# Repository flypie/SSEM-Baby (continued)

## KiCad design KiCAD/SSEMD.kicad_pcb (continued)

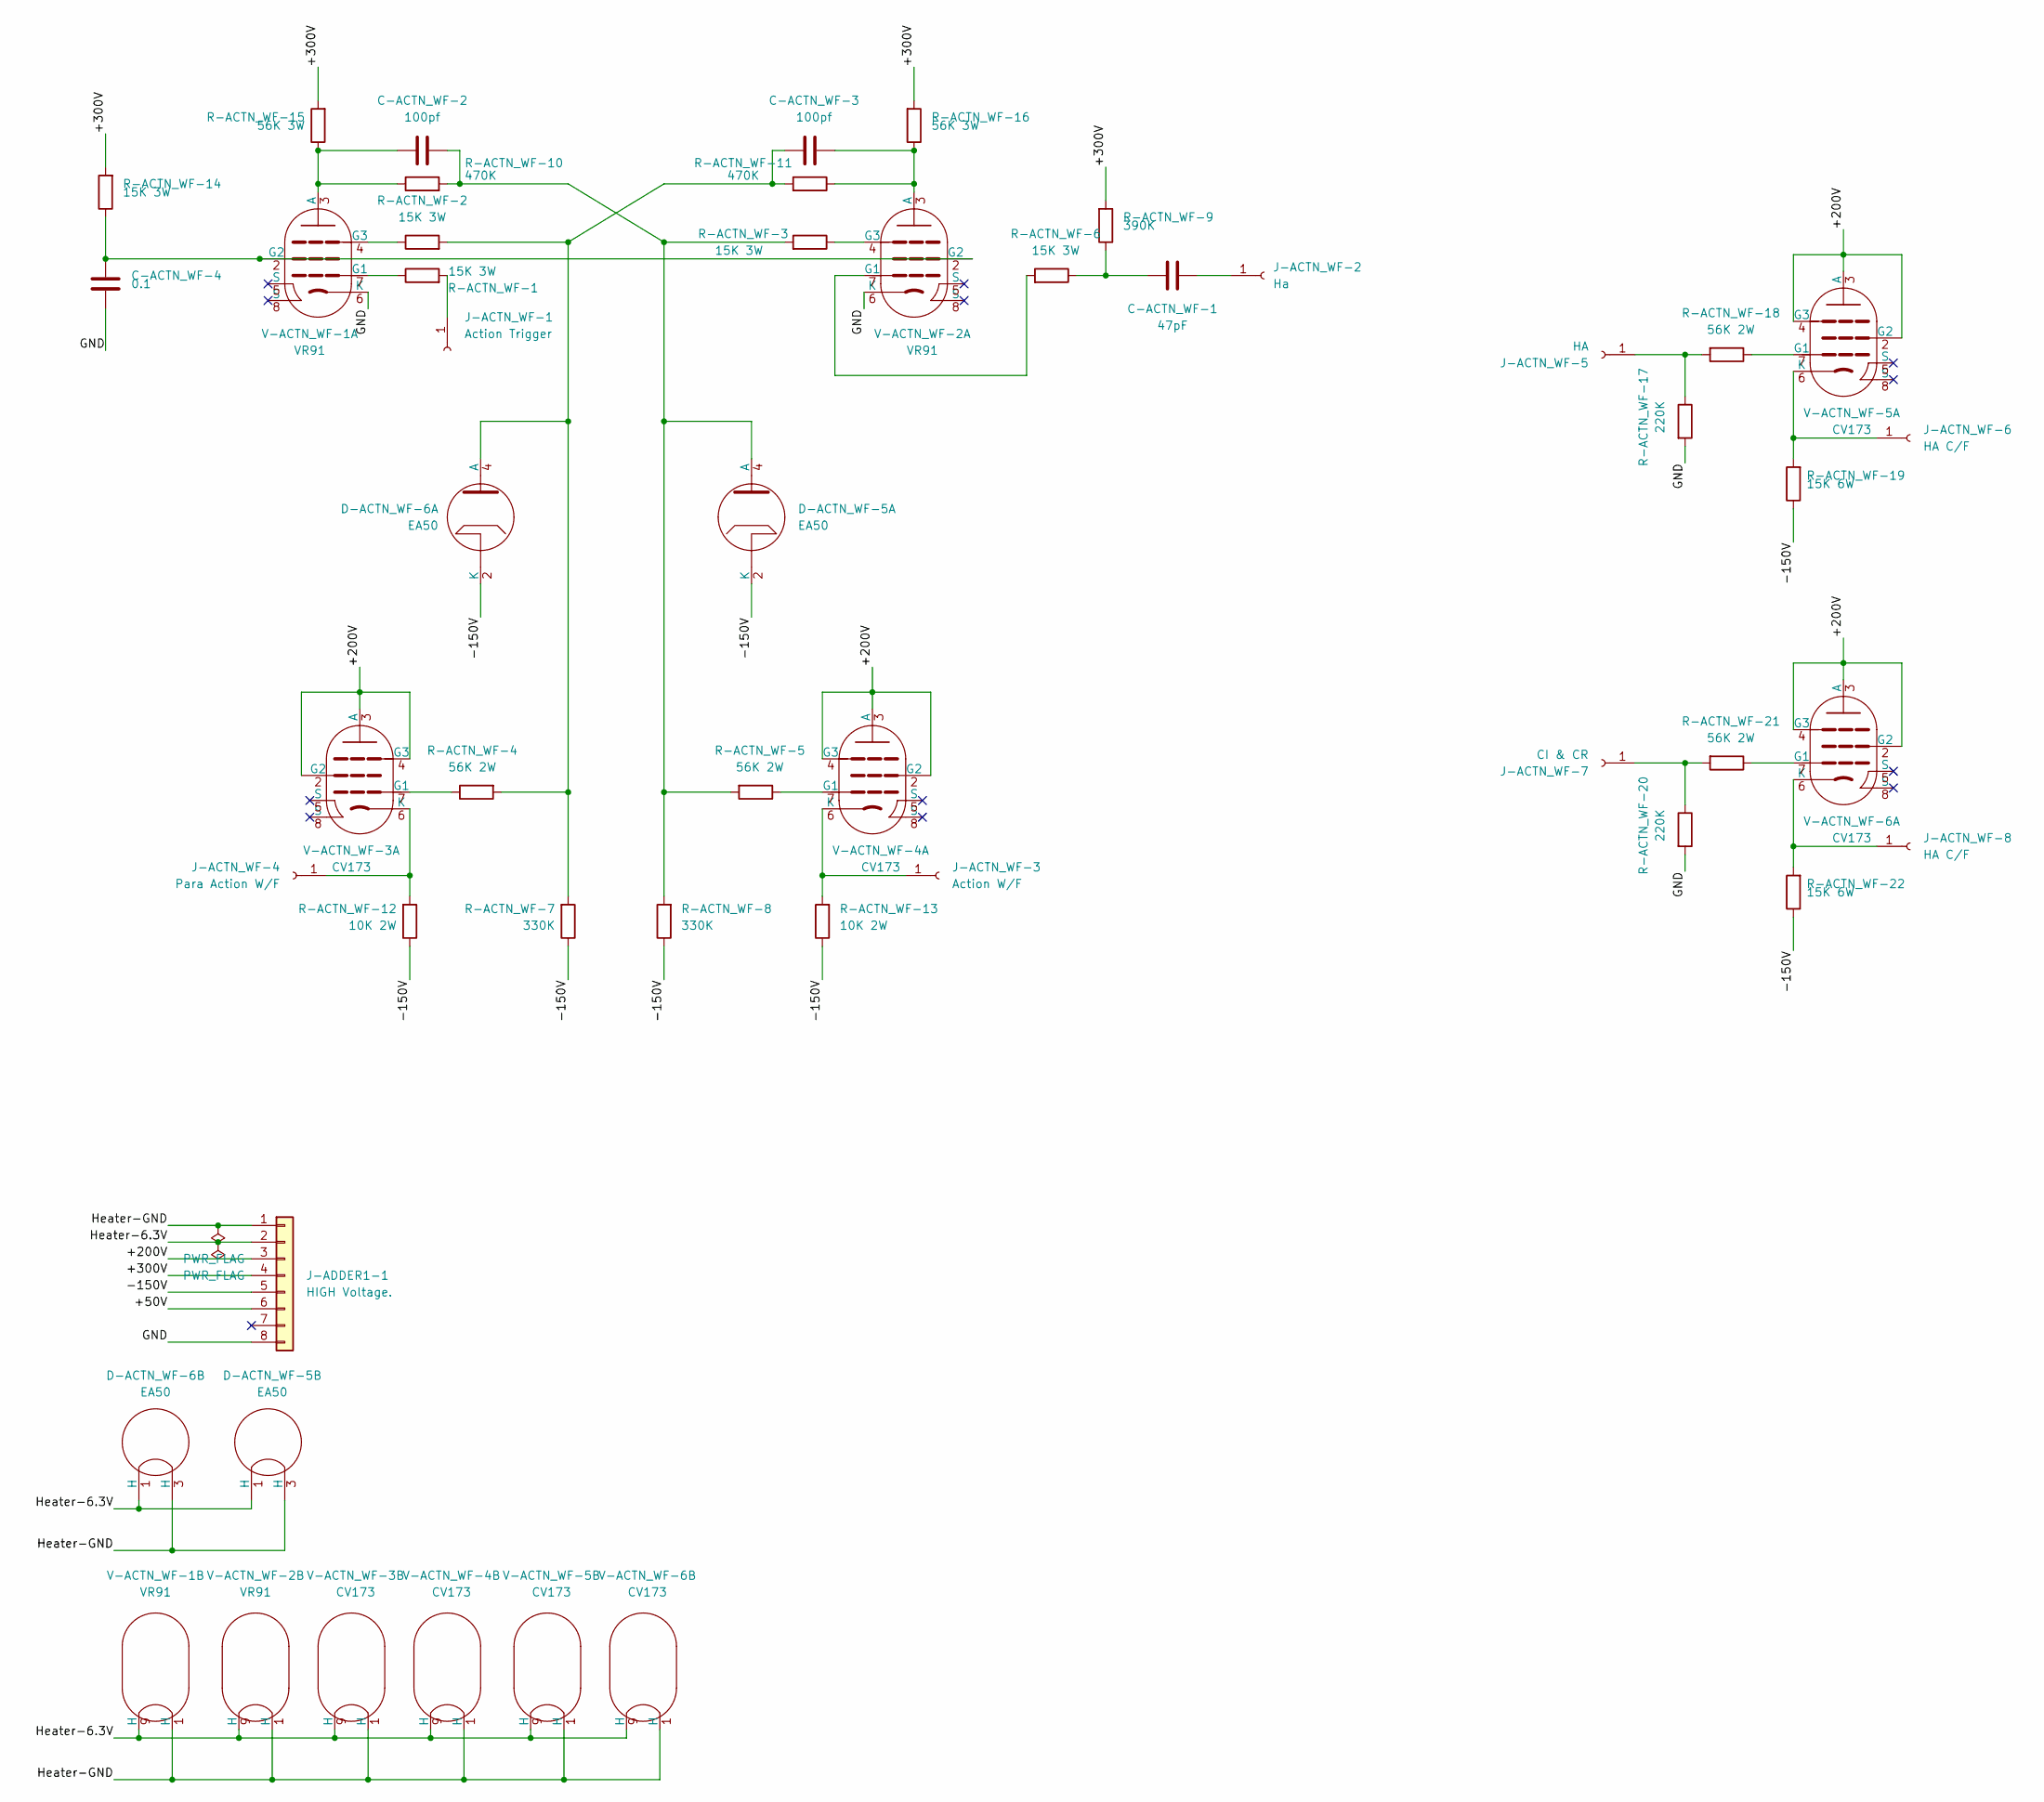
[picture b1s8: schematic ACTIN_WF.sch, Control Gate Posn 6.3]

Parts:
C-ACTN_WF-1: 47pF; C_Disc_D7.5mm_W5.0mm_P5.00mm
C-ACTN_WF-2, C-ACTN_WF-3: 100pf; C_Disc_D7.5mm_W5.0mm_P5.00mm
C-ACTN_WF-4: 0.1; C_Disc_D7.5mm_W5.0mm_P5.00mm
D-ACTN_WF-5, D-ACTN_WF-6: EA50; Valve_B3G
J-ACTN_WF-1: Action Trigger; 242431
J-ACTN_WF-2: Ha; 242431
J-ACTN_WF-3: Action W/F; 242431
J-ACTN_WF-4: Para Action W/F; 242431
J-ACTN_WF-5: HA; 242431
J-ACTN_WF-6, J-ACTN_WF-8: HA C/F; 242431
J-ACTN_WF-7: CI & CR; 242431
J-ADDER1-1: HIGH Voltage.; TE_MATE-N-LOK_1-770970-x_2x04_P4.14mm_Horizontal
R-ACTN_WF-1, R-ACTN_WF-2, R-ACTN_WF-3, R-ACTN_WF-6, R-ACTN_WF-14: 15K 3W; R_Axial_DIN0516_L15.5mm_D5.0mm_P5.08mm_Vertical
R-ACTN_WF-4, R-ACTN_WF-5, R-ACTN_WF-18, R-ACTN_WF-21: 56K 2W; R_Axial_DIN0516_L15.5mm_D5.0mm_P5.08mm_Vertical
R-ACTN_WF-7, R-ACTN_WF-8: 330K; R_Axial_DIN0516_L15.5mm_D5.0mm_P5.08mm_Vertical
R-ACTN_WF-9: 390K; R_Axial_DIN0516_L15.5mm_D5.0mm_P5.08mm_Vertical
R-ACTN_WF-10, R-ACTN_WF-11: 470K; R_Axial_DIN0516_L15.5mm_D5.0mm_P5.08mm_Vertical
R-ACTN_WF-12, R-ACTN_WF-13: 10K 2W; R_Axial_DIN0516_L15.5mm_D5.0mm_P5.08mm_Vertical
R-ACTN_WF-15, R-ACTN_WF-16: 56K 3W; R_Axial_DIN0516_L15.5mm_D5.0mm_P5.08mm_Vertical
R-ACTN_WF-17, R-ACTN_WF-20: 220K; R_Axial_DIN0516_L15.5mm_D5.0mm_P5.08mm_Vertical
R-ACTN_WF-19, R-ACTN_WF-22: 15K 6W; R_Axial_DIN0516_L15.5mm_D5.0mm_P5.08mm_Vertical
V-ACTN_WF-1, V-ACTN_WF-2: VR91; Valve_9Loctal
V-ACTN_WF-3, V-ACTN_WF-4, V-ACTN_WF-5, V-ACTN_WF-6: CV173; Valve_9Loctal

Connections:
/ACTIN_WF/+200V: J-ADDER1-1.3, V-ACTN_WF-3.2 (G2), V-ACTN_WF-3.3 (A), V-ACTN_WF-3.4 (G3), V-ACTN_WF-4.2 (G2), V-ACTN_WF-4.3 (A), V-ACTN_WF-4.4 (G3), V-ACTN_WF-5.2 (G2), V-ACTN_WF-5.3 (A), V-ACTN_WF-5.4 (G3), V-ACTN_WF-6.2 (G2), V-ACTN_WF-6.3 (A), V-ACTN_WF-6.4 (G3)
/ACTIN_WF/+300V: J-ADDER1-1.4, R-ACTN_WF-9.2, R-ACTN_WF-14.2, R-ACTN_WF-15.2, R-ACTN_WF-16.2
/ACTIN_WF/-150V: D-ACTN_WF-5.2 (K), D-ACTN_WF-6.2 (K), J-ADDER1-1.5, R-ACTN_WF-7.1, R-ACTN_WF-8.1, R-ACTN_WF-12.1, R-ACTN_WF-13.1, R-ACTN_WF-19.1, R-ACTN_WF-22.1
/ACTIN_WF/GND: C-ACTN_WF-4.2, J-ADDER1-1.8, R-ACTN_WF-17.2, R-ACTN_WF-20.2, V-ACTN_WF-1.6 (K), V-ACTN_WF-2.6 (K)
/ACTIN_WF/Heater-6.3V: D-ACTN_WF-5.1 (H), D-ACTN_WF-6.1 (H), J-ADDER1-1.2, V-ACTN_WF-1.9 (H), V-ACTN_WF-2.9 (H), V-ACTN_WF-3.9 (H), V-ACTN_WF-4.9 (F1), V-ACTN_WF-5.9 (H), V-ACTN_WF-6.9 (H)
/ACTIN_WF/Heater-GND: D-ACTN_WF-5.3 (H), D-ACTN_WF-6.3 (H), J-ADDER1-1.1, V-ACTN_WF-1.1 (H), V-ACTN_WF-2.1 (H), V-ACTN_WF-3.1 (H), V-ACTN_WF-4.1 (F1), V-ACTN_WF-5.1 (H), V-ACTN_WF-6.1 (H)
unnamed: C-ACTN_WF-1.1, J-ACTN_WF-2.1
unnamed: C-ACTN_WF-1.2, R-ACTN_WF-6.1, R-ACTN_WF-9.1
unnamed: C-ACTN_WF-2.1, R-ACTN_WF-10.1, R-ACTN_WF-15.1, V-ACTN_WF-1.3 (A)
unnamed: C-ACTN_WF-2.2, D-ACTN_WF-5.4 (A), R-ACTN_WF-3.2, R-ACTN_WF-5.2, R-ACTN_WF-8.2, R-ACTN_WF-10.2
unnamed: C-ACTN_WF-3.1, R-ACTN_WF-11.1, R-ACTN_WF-16.1, V-ACTN_WF-2.3 (A)
unnamed: C-ACTN_WF-3.2, D-ACTN_WF-6.4 (A), R-ACTN_WF-2.2, R-ACTN_WF-4.2, R-ACTN_WF-7.2, R-ACTN_WF-11.2
unnamed: C-ACTN_WF-4.1, R-ACTN_WF-14.1, V-ACTN_WF-1.2 (G2), V-ACTN_WF-2.2 (G2)
unnamed: J-ACTN_WF-1.1, R-ACTN_WF-1.2
unnamed: J-ACTN_WF-3.1, R-ACTN_WF-13.2, V-ACTN_WF-4.6 (K)
unnamed: J-ACTN_WF-4.1, R-ACTN_WF-12.2, V-ACTN_WF-3.6 (K)
unnamed: J-ACTN_WF-5.1, R-ACTN_WF-17.1, R-ACTN_WF-18.2
unnamed: J-ACTN_WF-6.1, R-ACTN_WF-19.2, V-ACTN_WF-5.6 (K)
unnamed: J-ACTN_WF-7.1, R-ACTN_WF-20.1, R-ACTN_WF-21.2
unnamed: J-ACTN_WF-8.1, R-ACTN_WF-22.2, V-ACTN_WF-6.6 (K)
unnamed: R-ACTN_WF-1.1, V-ACTN_WF-1.7 (G1)
unnamed: R-ACTN_WF-2.1, V-ACTN_WF-1.4 (G3)
unnamed: R-ACTN_WF-3.1, V-ACTN_WF-2.4 (G3)
unnamed: R-ACTN_WF-4.1, V-ACTN_WF-3.7 (G1)
unnamed: R-ACTN_WF-5.1, V-ACTN_WF-4.7 (G1)
unnamed: R-ACTN_WF-6.2, V-ACTN_WF-2.7 (G1)
unnamed: R-ACTN_WF-18.1, V-ACTN_WF-5.7 (G1)
unnamed: R-ACTN_WF-21.1, V-ACTN_WF-6.7 (G1)

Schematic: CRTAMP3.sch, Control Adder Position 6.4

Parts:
C-CRTAMP3-1: 18p; C_Disc_D7.5mm_W5.0mm_P5.00mm
C-CRTAMP3-2, C-CRTAMP3-12, C-CRTAMP3-22, C-CRTAMP3-30, C-CRTAMP3-36, C-CRTAMP3-42, C-CRTAMP3-47: 0.5; C_Disc_D7.5mm_W5.0mm_P5.00mm
C-CRTAMP3-3, C-CRTAMP3-13, C-CRTAMP3-23, C-CRTAMP3-37, C-CRTAMP3-43: 2U2; C_Disc_D7.5mm_W5.0mm_P5.00mm
C-CRTAMP3-4, C-CRTAMP3-6, C-CRTAMP3-14, C-CRTAMP3-17, C-CRTAMP3-26, C-CRTAMP3-28, C-CRTAMP3-32, C-CRTAMP3-34, C-CRTAMP3-38, C-CRTAMP3-40, C-CRTAMP3-44, C-CRTAMP3-46, C-CRTAMP3-48, C-CRTAMP3-49: 0.1; C_Disc_D7.5mm_W5.0mm_P5.00mm
C-CRTAMP3-5, C-CRTAMP3-15, C-CRTAMP3-27, C-CRTAMP3-33, C-CRTAMP3-39: 10u; C_Disc_D7.5mm_W5.0mm_P5.00mm
C-CRTAMP3-7, C-CRTAMP3-8, C-CRTAMP3-10, C-CRTAMP3-11, C-CRTAMP3-16, C-CRTAMP3-18, C-CRTAMP3-20, C-CRTAMP3-21, C-CRTAMP3-24, C-CRTAMP3-25: 270pf; C_Disc_D7.5mm_W5.0mm_P5.00mm
C-CRTAMP3-9, C-CRTAMP3-19, C-CRTAMP3-29, C-CRTAMP3-35, C-CRTAMP3-41: 750p; C_Disc_D7.5mm_W5.0mm_P5.00mm
C-CRTAMP3-31: 16U; C_Disc_D7.5mm_W5.0mm_P5.00mm
C-CRTAMP3-45: 0.01; C_Disc_D7.5mm_W5.0mm_P5.00mm
J-CRTAMP3-1: HIGH Voltage.; TE_MATE-N-LOK_1-770970-x_2x04_P4.14mm_Horizontal
J-CRTAMP3-2, J-CRTAMP3-3: PLUS1OR2; 242431
R-CRTAMP3-1, R-CRTAMP3-7, R-CRTAMP3-13, R-CRTAMP3-19, R-CRTAMP3-25, R-CRTAMP3-31, R-CRTAMP3-37, R-CRTAMP3-41: 1M; R_Axial_DIN0516_L15.5mm_D5.0mm_P5.08mm_Vertical
R-CRTAMP3-2, R-CRTAMP3-8, R-CRTAMP3-14, R-CRTAMP3-20, R-CRTAMP3-26, R-CRTAMP3-32: 33; R_Axial_DIN0516_L15.5mm_D5.0mm_P5.08mm_Vertical
R-CRTAMP3-3, R-CRTAMP3-9, R-CRTAMP3-15, R-CRTAMP3-21, R-CRTAMP3-27, R-CRTAMP3-33: 150; R_Axial_DIN0516_L15.5mm_D5.0mm_P5.08mm_Vertical
R-CRTAMP3-4, R-CRTAMP3-10, R-CRTAMP3-16, R-CRTAMP3-22, R-CRTAMP3-28, R-CRTAMP3-34: 10K; R_Axial_DIN0516_L15.5mm_D5.0mm_P5.08mm_Vertical
R-CRTAMP3-5, R-CRTAMP3-11, R-CRTAMP3-17, R-CRTAMP3-23, R-CRTAMP3-29, R-CRTAMP3-35: 1K2; R_Axial_DIN0516_L15.5mm_D5.0mm_P5.08mm_Vertical
R-CRTAMP3-6, R-CRTAMP3-12, R-CRTAMP3-18, R-CRTAMP3-24, R-CRTAMP3-30, R-CRTAMP3-36: 8K2; R_Axial_DIN0516_L15.5mm_D5.0mm_P5.08mm_Vertical
R-CRTAMP3-38: 33K; R_Axial_DIN0516_L15.5mm_D5.0mm_P5.08mm_Vertical
R-CRTAMP3-39: 5K; R_Axial_DIN0516_L15.5mm_D5.0mm_P5.08mm_Vertical
R-CRTAMP3-40: 56K; R_Axial_DIN0516_L15.5mm_D5.0mm_P5.08mm_Vertical
R-CRTAMP3-42: 50K; R_Axial_DIN0516_L15.5mm_D5.0mm_P5.08mm_Vertical
V-CRTAMP3-1, V-CRTAMP3-2, V-CRTAMP3-3, V-CRTAMP3-4, V-CRTAMP3-5, V-CRTAMP3-6: CV173; Valve_9Loctal

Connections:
/CRTAMP3/+300: C-CRTAMP3-2.1, C-CRTAMP3-12.1, C-CRTAMP3-22.1, C-CRTAMP3-30.1, C-CRTAMP3-36.1, C-CRTAMP3-42.1, C-CRTAMP3-44.1, R-CRTAMP3-4.1, R-CRTAMP3-6.1, R-CRTAMP3-10.1, R-CRTAMP3-12.1, R-CRTAMP3-16.1, R-CRTAMP3-18.1, R-CRTAMP3-22.1, R-CRTAMP3-24.1, R-CRTAMP3-28.1, R-CRTAMP3-30.1, R-CRTAMP3-34.1, R-CRTAMP3-36.1, R-CRTAMP3-42.1
/CRTAMP3/-150V: C-CRTAMP3-47.1, J-CRTAMP3-1.5, R-CRTAMP3-40.1
/CRTAMP3/GND: C-CRTAMP3-2.2, C-CRTAMP3-3.2, C-CRTAMP3-5.2, C-CRTAMP3-6.2, C-CRTAMP3-7.1, C-CRTAMP3-8.2, C-CRTAMP3-10.1, C-CRTAMP3-11.2, C-CRTAMP3-12.2, C-CRTAMP3-13.2, C-CRTAMP3-15.2, C-CRTAMP3-16.1, C-CRTAMP3-17.2, C-CRTAMP3-18.2, C-CRTAMP3-20.1, C-CRTAMP3-21.2, C-CRTAMP3-22.2, C-CRTAMP3-23.2, C-CRTAMP3-24.1, C-CRTAMP3-25.2, C-CRTAMP3-27.2, C-CRTAMP3-28.2, C-CRTAMP3-30.2, C-CRTAMP3-31.2, C-CRTAMP3-33.2, C-CRTAMP3-34.2, C-CRTAMP3-36.2, C-CRTAMP3-37.2, C-CRTAMP3-39.2, C-CRTAMP3-40.2, C-CRTAMP3-42.2, C-CRTAMP3-43.2, C-CRTAMP3-44.2, C-CRTAMP3-46.2, C-CRTAMP3-47.2, C-CRTAMP3-49.2, J-CRTAMP3-1.8, R-CRTAMP3-1.1, R-CRTAMP3-3.1, R-CRTAMP3-7.1, R-CRTAMP3-9.1, R-CRTAMP3-13.1, R-CRTAMP3-15.1, R-CRTAMP3-19.1, R-CRTAMP3-21.1, R-CRTAMP3-25.1, R-CRTAMP3-27.1, R-CRTAMP3-31.1, R-CRTAMP3-33.1, R-CRTAMP3-33.2, R-CRTAMP3-42.2, V-CRTAMP3-6.4 (G3), V-CRTAMP3-6.6 (K)
/CRTAMP3/Heater-6.3V: C-CRTAMP3-7.2, C-CRTAMP3-10.2, C-CRTAMP3-16.2, C-CRTAMP3-20.2, J-CRTAMP3-1.2, V-CRTAMP3-1.9 (F1), V-CRTAMP3-2.9 (F1), V-CRTAMP3-3.9 (F1), V-CRTAMP3-4.9 (F1)
/CRTAMP3/Heater-GND: C-CRTAMP3-8.1, C-CRTAMP3-11.1, C-CRTAMP3-18.1, C-CRTAMP3-21.1, C-CRTAMP3-25.1, J-CRTAMP3-1.1, V-CRTAMP3-1.1 (F1), V-CRTAMP3-2.1 (F1), V-CRTAMP3-3.1 (F1), V-CRTAMP3-4.1 (F1), V-CRTAMP3-5.1 (F1), V-CRTAMP3-6.1 (F1)
unnamed: C-CRTAMP3-1.1, C-CRTAMP3-9.1, C-CRTAMP3-19.1, C-CRTAMP3-29.1, C-CRTAMP3-35.1, C-CRTAMP3-41.1, C-CRTAMP3-48.1, R-CRTAMP3-5.2, R-CRTAMP3-11.2, R-CRTAMP3-17.2, R-CRTAMP3-23.2, R-CRTAMP3-29.2, R-CRTAMP3-35.2, R-CRTAMP3-38.1, R-CRTAMP3-39.2, V-CRTAMP3-1.3 (A), V-CRTAMP3-2.3 (A), V-CRTAMP3-3.3 (A), V-CRTAMP3-4.3 (A), V-CRTAMP3-5.3 (A), V-CRTAMP3-6.3 (A)
unnamed: C-CRTAMP3-1.2, J-CRTAMP3-2.1, R-CRTAMP3-1.2, R-CRTAMP3-2.2, R-CRTAMP3-37.1
unnamed: C-CRTAMP3-3.1, R-CRTAMP3-4.2, R-CRTAMP3-5.1
unnamed: C-CRTAMP3-4.1, R-CRTAMP3-6.2, V-CRTAMP3-1.2 (G2)
unnamed: C-CRTAMP3-4.2, C-CRTAMP3-5.1, C-CRTAMP3-6.1, R-CRTAMP3-3.2, V-CRTAMP3-1.4 (G3), V-CRTAMP3-1.6 (K)
unnamed: C-CRTAMP3-9.2, R-CRTAMP3-7.2, R-CRTAMP3-8.2
unnamed: C-CRTAMP3-13.1, R-CRTAMP3-10.2, R-CRTAMP3-11.1
unnamed: C-CRTAMP3-14.1, R-CRTAMP3-12.2, V-CRTAMP3-2.2 (G2)
unnamed: C-CRTAMP3-14.2, C-CRTAMP3-15.1, C-CRTAMP3-17.1, R-CRTAMP3-9.2, V-CRTAMP3-2.4 (G3), V-CRTAMP3-2.6 (K)
unnamed: C-CRTAMP3-19.2, R-CRTAMP3-13.2, R-CRTAMP3-14.2
unnamed: C-CRTAMP3-23.1, R-CRTAMP3-16.2, R-CRTAMP3-17.1
unnamed: C-CRTAMP3-24.2, V-CRTAMP3-5.9 (F1), V-CRTAMP3-6.9 (F1)
unnamed: C-CRTAMP3-26.1, R-CRTAMP3-18.2, V-CRTAMP3-3.2 (G2)
unnamed: C-CRTAMP3-26.2, C-CRTAMP3-27.1, C-CRTAMP3-28.1, R-CRTAMP3-15.2, V-CRTAMP3-3.4 (G3), V-CRTAMP3-3.6 (K)
unnamed: C-CRTAMP3-29.2, R-CRTAMP3-19.2, R-CRTAMP3-20.2
unnamed: C-CRTAMP3-31.1, R-CRTAMP3-22.2, R-CRTAMP3-23.1
unnamed: C-CRTAMP3-32.1, R-CRTAMP3-24.2, R-CRTAMP3-41.2, V-CRTAMP3-4.2 (G2)
unnamed: C-CRTAMP3-32.2, C-CRTAMP3-33.1, C-CRTAMP3-34.1, R-CRTAMP3-21.2, V-CRTAMP3-4.4 (G3), V-CRTAMP3-4.6 (K)
unnamed: C-CRTAMP3-35.2, R-CRTAMP3-25.2, R-CRTAMP3-26.2
unnamed: C-CRTAMP3-37.1, R-CRTAMP3-28.2, R-CRTAMP3-29.1
unnamed: C-CRTAMP3-38.1, R-CRTAMP3-30.2, V-CRTAMP3-5.2 (G2)
unnamed: C-CRTAMP3-38.2, C-CRTAMP3-39.1, C-CRTAMP3-40.1, R-CRTAMP3-27.2, V-CRTAMP3-5.4 (G3), V-CRTAMP3-5.6 (K)
unnamed: C-CRTAMP3-41.2, R-CRTAMP3-31.2, R-CRTAMP3-32.2
unnamed: C-CRTAMP3-43.1, R-CRTAMP3-34.2, R-CRTAMP3-35.1
unnamed: C-CRTAMP3-45.1, R-CRTAMP3-38.2
unnamed: C-CRTAMP3-45.2, J-CRTAMP3-3.1
unnamed: C-CRTAMP3-46.1, R-CRTAMP3-36.2, V-CRTAMP3-6.2 (G2)
unnamed: C-CRTAMP3-48.2, R-CRTAMP3-37.2
unnamed: C-CRTAMP3-49.1, R-CRTAMP3-41.1
unnamed: R-CRTAMP3-2.1, V-CRTAMP3-1.7 (G1)
unnamed: R-CRTAMP3-8.1, V-CRTAMP3-2.7 (G1)
unnamed: R-CRTAMP3-14.1, V-CRTAMP3-3.7 (G1)
unnamed: R-CRTAMP3-20.1, V-CRTAMP3-4.7 (G1)
unnamed: R-CRTAMP3-26.1, V-CRTAMP3-5.7 (G1)
unnamed: R-CRTAMP3-32.1, V-CRTAMP3-6.7 (G1)
unnamed: R-CRTAMP3-39.1, R-CRTAMP3-40.2

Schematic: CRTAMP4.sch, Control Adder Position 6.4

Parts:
C-CRTAMP4-1: 18p; C_Trimmer_Voltronics_JZ
C-CRTAMP4-2, C-CRTAMP4-12, C-CRTAMP4-22, C-CRTAMP4-31, C-CRTAMP4-38, C-CRTAMP4-44, C-CRTAMP4-47: 0.5; C_Disc_D7.5mm_W5.0mm_P5.00mm
C-CRTAMP4-3, C-CRTAMP4-13, C-CRTAMP4-23, C-CRTAMP4-32, C-CRTAMP4-39, C-CRTAMP4-45: 2U2; C_Disc_D7.5mm_W5.0mm_P5.00mm
C-CRTAMP4-4, C-CRTAMP4-6, C-CRTAMP4-14, C-CRTAMP4-17, C-CRTAMP4-26, C-CRTAMP4-28, C-CRTAMP4-29, C-CRTAMP4-33, C-CRTAMP4-35, C-CRTAMP4-36, C-CRTAMP4-40, C-CRTAMP4-42, C-CRTAMP4-46, C-CRTAMP4-48: 0.1; C_Disc_D7.5mm_W5.0mm_P5.00mm
C-CRTAMP4-5, C-CRTAMP4-15, C-CRTAMP4-27, C-CRTAMP4-34, C-CRTAMP4-41: 2u2; C_Disc_D7.5mm_W5.0mm_P5.00mm
C-CRTAMP4-7, C-CRTAMP4-8, C-CRTAMP4-10, C-CRTAMP4-11, C-CRTAMP4-16, C-CRTAMP4-18, C-CRTAMP4-20, C-CRTAMP4-21, C-CRTAMP4-24, C-CRTAMP4-25: 270pf; C_Disc_D7.5mm_W5.0mm_P5.00mm
C-CRTAMP4-9, C-CRTAMP4-19, C-CRTAMP4-30, C-CRTAMP4-37, C-CRTAMP4-43: 750p; C_Disc_D7.5mm_W5.0mm_P5.00mm
C-CRTAMP4-49: 0.01; C_Disc_D7.5mm_W5.0mm_P5.00mm
C-CRTAMP4-50: 8u; C_Disc_D7.5mm_W5.0mm_P5.00mm
J-CRTAMP4-1, J-CRTAMP4-3: PLUS1OR2; 242431
J-CRTAMP4-2: HIGH Voltage.; TE_MATE-N-LOK_1-770970-x_2x04_P4.14mm_Horizontal
R-CRTAMP4-1, R-CRTAMP4-7, R-CRTAMP4-12, R-CRTAMP4-14, R-CRTAMP4-20, R-CRTAMP4-26, R-CRTAMP4-28, R-CRTAMP4-34: 1M; R_Axial_DIN0516_L15.5mm_D5.0mm_P5.08mm_Vertical
R-CRTAMP4-2, R-CRTAMP4-8, R-CRTAMP4-15, R-CRTAMP4-21, R-CRTAMP4-29, R-CRTAMP4-35: 33; R_Axial_DIN0516_L15.5mm_D5.0mm_P5.08mm_Vertical
R-CRTAMP4-3, R-CRTAMP4-9, R-CRTAMP4-16, R-CRTAMP4-22, R-CRTAMP4-30, R-CRTAMP4-36: 150; R_Axial_DIN0516_L15.5mm_D5.0mm_P5.08mm_Vertical
R-CRTAMP4-4, R-CRTAMP4-10, R-CRTAMP4-17, R-CRTAMP4-23, R-CRTAMP4-31, R-CRTAMP4-37: 10K; R_Axial_DIN0516_L15.5mm_D5.0mm_P5.08mm_Vertical
R-CRTAMP4-5, R-CRTAMP4-11, R-CRTAMP4-18, R-CRTAMP4-24, R-CRTAMP4-32, R-CRTAMP4-38: 1K2; R_Axial_DIN0516_L15.5mm_D5.0mm_P5.08mm_Vertical
R-CRTAMP4-6, R-CRTAMP4-13, R-CRTAMP4-19, R-CRTAMP4-25, R-CRTAMP4-33, R-CRTAMP4-39: 8K2; R_Axial_DIN0516_L15.5mm_D5.0mm_P5.08mm_Vertical
R-CRTAMP4-27: 50K; R_Axial_DIN0516_L15.5mm_D5.0mm_P5.08mm_Vertical
R-CRTAMP4-40: 33K; R_Axial_DIN0516_L15.5mm_D5.0mm_P5.08mm_Vertical
R-CRTAMP4-41: 5K; R_Axial_DIN0516_L15.5mm_D5.0mm_P5.08mm_Vertical
R-CRTAMP4-42: 56K; R_Axial_DIN0516_L15.5mm_D5.0mm_P5.08mm_Vertical
V-CRTAMP4-1, V-CRTAMP4-2, V-CRTAMP4-3, V-CRTAMP4-4, V-CRTAMP4-5, V-CRTAMP4-6: CV173; Valve_9Loctal

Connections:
/CRTAMP4/+300: C-CRTAMP4-2.1, C-CRTAMP4-12.1, C-CRTAMP4-22.1, C-CRTAMP4-31.1, C-CRTAMP4-38.1, C-CRTAMP4-44.1, C-CRTAMP4-48.1, R-CRTAMP4-4.1, R-CRTAMP4-6.1, R-CRTAMP4-10.1, R-CRTAMP4-13.1, R-CRTAMP4-17.1, R-CRTAMP4-19.1, R-CRTAMP4-23.1, R-CRTAMP4-25.1, R-CRTAMP4-27.1, R-CRTAMP4-31.1, R-CRTAMP4-33.1, R-CRTAMP4-37.1, R-CRTAMP4-39.1
/CRTAMP4/-150V: C-CRTAMP4-47.1, J-CRTAMP4-2.5, R-CRTAMP4-42.1
/CRTAMP4/GND: C-CRTAMP4-2.2, C-CRTAMP4-3.2, C-CRTAMP4-5.2, C-CRTAMP4-6.2, C-CRTAMP4-7.1, C-CRTAMP4-8.2, C-CRTAMP4-10.1, C-CRTAMP4-11.2, C-CRTAMP4-12.2, C-CRTAMP4-13.2, C-CRTAMP4-15.2, C-CRTAMP4-16.1, C-CRTAMP4-17.2, C-CRTAMP4-18.2, C-CRTAMP4-20.1, C-CRTAMP4-21.2, C-CRTAMP4-22.2, C-CRTAMP4-23.2, C-CRTAMP4-24.1, C-CRTAMP4-25.2, C-CRTAMP4-27.2, C-CRTAMP4-28.2, C-CRTAMP4-31.2, C-CRTAMP4-32.2, C-CRTAMP4-34.2, C-CRTAMP4-35.2, C-CRTAMP4-36.2, C-CRTAMP4-38.2, C-CRTAMP4-39.2, C-CRTAMP4-41.2, C-CRTAMP4-42.2, C-CRTAMP4-44.2, C-CRTAMP4-45.2, C-CRTAMP4-46.2, C-CRTAMP4-47.2, C-CRTAMP4-48.2, C-CRTAMP4-50.2, J-CRTAMP4-2.8, R-CRTAMP4-1.1, R-CRTAMP4-3.1, R-CRTAMP4-7.1, R-CRTAMP4-9.1, R-CRTAMP4-14.1, R-CRTAMP4-16.1, R-CRTAMP4-20.1, R-CRTAMP4-22.1, R-CRTAMP4-27.2, R-CRTAMP4-28.1, R-CRTAMP4-30.1, R-CRTAMP4-34.1, R-CRTAMP4-36.1, R-CRTAMP4-36.2, V-CRTAMP4-6.4 (G3), V-CRTAMP4-6.6 (K)
/CRTAMP4/Heater-6.3V: C-CRTAMP4-7.2, C-CRTAMP4-10.2, C-CRTAMP4-16.2, C-CRTAMP4-20.2, J-CRTAMP4-2.2, V-CRTAMP4-1.9 (F1), V-CRTAMP4-2.9 (F1), V-CRTAMP4-3.9 (F1), V-CRTAMP4-4.9 (F1)
/CRTAMP4/Heater-GND: C-CRTAMP4-8.1, C-CRTAMP4-11.1, C-CRTAMP4-18.1, C-CRTAMP4-21.1, C-CRTAMP4-25.1, J-CRTAMP4-2.1, V-CRTAMP4-1.1 (F1), V-CRTAMP4-2.1 (F1), V-CRTAMP4-3.1 (F1), V-CRTAMP4-4.1 (F1), V-CRTAMP4-5.1 (F1), V-CRTAMP4-6.1 (F1)
unnamed: C-CRTAMP4-1.1, C-CRTAMP4-9.1, C-CRTAMP4-19.1, C-CRTAMP4-29.1, C-CRTAMP4-30.1, C-CRTAMP4-37.1, C-CRTAMP4-43.1, R-CRTAMP4-5.2, R-CRTAMP4-11.2, R-CRTAMP4-18.2, R-CRTAMP4-24.2, R-CRTAMP4-32.2, R-CRTAMP4-38.2, R-CRTAMP4-40.1, R-CRTAMP4-41.2, V-CRTAMP4-1.3 (A), V-CRTAMP4-2.3 (A), V-CRTAMP4-3.3 (A), V-CRTAMP4-4.3 (A), V-CRTAMP4-5.3 (A), V-CRTAMP4-6.3 (A)
unnamed: C-CRTAMP4-1.2, J-CRTAMP4-1.1, R-CRTAMP4-1.2, R-CRTAMP4-2.2, R-CRTAMP4-12.1
unnamed: C-CRTAMP4-3.1, R-CRTAMP4-4.2, R-CRTAMP4-5.1
unnamed: C-CRTAMP4-4.1, R-CRTAMP4-6.2, V-CRTAMP4-1.2 (G2)
unnamed: C-CRTAMP4-4.2, C-CRTAMP4-5.1, C-CRTAMP4-6.1, R-CRTAMP4-3.2, V-CRTAMP4-1.4 (G3), V-CRTAMP4-1.6 (K)
unnamed: C-CRTAMP4-9.2, R-CRTAMP4-7.2, R-CRTAMP4-8.2
unnamed: C-CRTAMP4-13.1, R-CRTAMP4-10.2, R-CRTAMP4-11.1
unnamed: C-CRTAMP4-14.1, R-CRTAMP4-13.2, V-CRTAMP4-2.2 (G2)
unnamed: C-CRTAMP4-14.2, C-CRTAMP4-15.1, C-CRTAMP4-17.1, R-CRTAMP4-9.2, V-CRTAMP4-2.4 (G3), V-CRTAMP4-2.6 (K)
unnamed: C-CRTAMP4-19.2, R-CRTAMP4-14.2, R-CRTAMP4-15.2
unnamed: C-CRTAMP4-23.1, R-CRTAMP4-17.2, R-CRTAMP4-18.1
unnamed: C-CRTAMP4-24.2, V-CRTAMP4-5.9 (F1), V-CRTAMP4-6.9 (F1)
unnamed: C-CRTAMP4-26.1, R-CRTAMP4-19.2, V-CRTAMP4-3.2 (G2)
unnamed: C-CRTAMP4-26.2, C-CRTAMP4-27.1, C-CRTAMP4-28.1, R-CRTAMP4-16.2, V-CRTAMP4-3.4 (G3), V-CRTAMP4-3.6 (K)
unnamed: C-CRTAMP4-29.2, R-CRTAMP4-12.2
unnamed: C-CRTAMP4-30.2, R-CRTAMP4-20.2, R-CRTAMP4-21.2
unnamed: C-CRTAMP4-32.1, C-CRTAMP4-50.1, R-CRTAMP4-23.2, R-CRTAMP4-24.1
unnamed: C-CRTAMP4-33.1, R-CRTAMP4-25.2, R-CRTAMP4-26.2, V-CRTAMP4-4.2 (G2)
unnamed: C-CRTAMP4-33.2, C-CRTAMP4-34.1, C-CRTAMP4-35.1, R-CRTAMP4-22.2, V-CRTAMP4-4.4 (G3), V-CRTAMP4-4.6 (K)
unnamed: C-CRTAMP4-36.1, R-CRTAMP4-26.1
unnamed: C-CRTAMP4-37.2, R-CRTAMP4-28.2, R-CRTAMP4-29.2
unnamed: C-CRTAMP4-39.1, R-CRTAMP4-31.2, R-CRTAMP4-32.1
unnamed: C-CRTAMP4-40.1, R-CRTAMP4-33.2, V-CRTAMP4-5.2 (G2)
unnamed: C-CRTAMP4-40.2, C-CRTAMP4-41.1, C-CRTAMP4-42.1, R-CRTAMP4-30.2, V-CRTAMP4-5.4 (G3), V-CRTAMP4-5.6 (K)
unnamed: C-CRTAMP4-43.2, R-CRTAMP4-34.2, R-CRTAMP4-35.2
unnamed: C-CRTAMP4-45.1, R-CRTAMP4-37.2, R-CRTAMP4-38.1
unnamed: C-CRTAMP4-46.1, R-CRTAMP4-39.2, V-CRTAMP4-6.2 (G2)
unnamed: C-CRTAMP4-49.1, R-CRTAMP4-40.2
unnamed: C-CRTAMP4-49.2, J-CRTAMP4-3.1
unnamed: R-CRTAMP4-2.1, V-CRTAMP4-1.7 (G1)
unnamed: R-CRTAMP4-8.1, V-CRTAMP4-2.7 (G1)
unnamed: R-CRTAMP4-15.1, V-CRTAMP4-3.7 (G1)
unnamed: R-CRTAMP4-21.1, V-CRTAMP4-4.7 (G1)
unnamed: R-CRTAMP4-29.1, V-CRTAMP4-5.7 (G1)
unnamed: R-CRTAMP4-35.1, V-CRTAMP4-6.7 (G1)
unnamed: R-CRTAMP4-41.1, R-CRTAMP4-42.2

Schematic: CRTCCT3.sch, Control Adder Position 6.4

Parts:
C-CRTCCT3-1: 0.25 4kV; C_Disc_D7.5mm_W5.0mm_P5.00mm
C-CRTCCT3-2, C-CRTCCT3-3, C-CRTCCT3-4: 0.1; C_Disc_D7.5mm_W5.0mm_P5.00mm
C-CRTCCT3-5: 0.5 350V; C_Disc_D7.5mm_W5.0mm_P5.00mm
C-CRTCCT3-6: 0.01 4kV; C_Disc_D7.5mm_W5.0mm_P5.00mm
C-CRTCCT3-7: 0.03 4kv; C_Disc_D7.5mm_W5.0mm_P5.00mm
D-CRTCCT3-1: VR78; Valve_B3G
J-CRTCCT3-1: Y2; 242431
J-CRTCCT3-2: X2; 242431
J-CRTCCT3-3: Y1; 242431
J-CRTCCT3-4: X1; 242431
J-CRTCCT3-5, J-CRTCCT3-8: S.PLATE; 242431
J-CRTCCT3-6: HIGH Voltage.; TE_MATE-N-LOK_1-770970-x_2x04_P4.14mm_Horizontal
J-CRTCCT3-7: +300; 242431
R-CRTCCT3-1, R-CRTCCT3-2, R-CRTCCT3-3: 680K; R_Axial_DIN0516_L15.5mm_D5.0mm_P5.08mm_Vertical
R-CRTCCT3-4: 470K; R_Axial_DIN0516_L15.5mm_D5.0mm_P5.08mm_Vertical
R-CRTCCT3-5: 270K; R_Axial_DIN0516_L15.5mm_D5.0mm_P5.08mm_Vertical
R-CRTCCT3-6: 2M2; R_Axial_DIN0516_L15.5mm_D5.0mm_P5.08mm_Vertical
R-CRTCCT3-7: 22K; R_Axial_DIN0516_L15.5mm_D5.0mm_P5.08mm_Vertical
RV-CRTCCT3-1: 500K; Potentiometer_Bourns_3339P_Vertical_HandSoldering
RV-CRTCCT3-2, RV-CRTCCT3-3: 100K; Potentiometer_Bourns_3339P_Vertical_HandSoldering
V-CRTCCT3-1: VCR97; B12D

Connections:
/CRTCCT3/GND: C-CRTCCT3-1.2, C-CRTCCT3-2.1, C-CRTCCT3-3.1, C-CRTCCT3-6.2, J-CRTCCT3-5.2 (Ext), J-CRTCCT3-6.8, J-CRTCCT3-7.2 (Ext), J-CRTCCT3-8.2 (Ext), R-CRTCCT3-1.2, RV-CRTCCT3-2.1
/CRTCCT3/Heater-6.3V: C-CRTCCT3-4.2, C-CRTCCT3-5.1, D-CRTCCT3-1.1 (J), J-CRTCCT3-6.2, RV-CRTCCT3-3.2, V-CRTCCT3-1.2 (K), V-CRTCCT3-1.3 (h)
/CRTCCT3/Heater-GND: C-CRTCCT3-4.1, D-CRTCCT3-1.3 (J), J-CRTCCT3-6.1, V-CRTCCT3-1.4 (h)
/CRTCCT3/S.EHT(800-1400V): C-CRTCCT3-5.2, C-CRTCCT3-6.1, D-CRTCCT3-1.2 (K), R-CRTCCT3-6.1, R-CRTCCT3-7.1
unnamed: C-CRTCCT3-1.1, R-CRTCCT3-4.1, V-CRTCCT3-1.6 (A2)
unnamed: C-CRTCCT3-2.2, RV-CRTCCT3-2.2, V-CRTCCT3-1.5 (A1), V-CRTCCT3-1.7 (CC), V-CRTCCT3-1.10 (A3)
unnamed: C-CRTCCT3-3.2, J-CRTCCT3-7.1 (In), RV-CRTCCT3-2.3
unnamed: C-CRTCCT3-7.1, J-CRTCCT3-8.1 (In)
unnamed: C-CRTCCT3-7.2, D-CRTCCT3-1.4 (A), R-CRTCCT3-6.2, V-CRTCCT3-1.1 (G1)
unnamed: J-CRTCCT3-1.1, V-CRTCCT3-1.8 (y2)
unnamed: J-CRTCCT3-2.1, V-CRTCCT3-1.9 (x2)
unnamed: J-CRTCCT3-3.1, V-CRTCCT3-1.12 (y1)
unnamed: J-CRTCCT3-4.1, V-CRTCCT3-1.11 (x1)
unnamed: R-CRTCCT3-1.1, R-CRTCCT3-2.2
unnamed: R-CRTCCT3-2.1, R-CRTCCT3-3.2
unnamed: R-CRTCCT3-3.1, RV-CRTCCT3-1.1
unnamed: R-CRTCCT3-4.2, RV-CRTCCT3-1.2
unnamed: R-CRTCCT3-5.1, RV-CRTCCT3-3.1
unnamed: R-CRTCCT3-5.2, RV-CRTCCT3-1.3
unnamed: R-CRTCCT3-7.2, RV-CRTCCT3-3.3

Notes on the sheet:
ASTIG
FOCUS
BRILL

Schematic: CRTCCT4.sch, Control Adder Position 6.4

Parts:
C-CRTCCT4-1: 0.25 4kV; C_Disc_D7.5mm_W5.0mm_P5.00mm
C-CRTCCT4-2, C-CRTCCT4-3, C-CRTCCT4-4: 0.1; C_Disc_D7.5mm_W5.0mm_P5.00mm
C-CRTCCT4-5: 0.5 350V; C_Disc_D7.5mm_W5.0mm_P5.00mm
C-CRTCCT4-6: 0.01 4kV; C_Disc_D7.5mm_W5.0mm_P5.00mm
C-CRTCCT4-7: 0.03 4kv; C_Disc_D7.5mm_W5.0mm_P5.00mm
D-CRTCCT4-1: VR78; Valve_B3G
J-CRTCCT4-1: C.PLATE; 242431
J-CRTCCT4-2: C.Y2; 242431
J-CRTCCT4-3: C.Y1; 242431
J-CRTCCT4-4: C.X2; 242431
J-CRTCCT4-5: C.X1; 242431
J-CRTCCT4-6: +300; 242431
J-CRTCCT4-7: C.GRID; 242431
J-CRTCCT4-15: HIGH Voltage.; TE_MATE-N-LOK_1-770970-x_2x04_P4.14mm_Horizontal
R-CRTCCT4-1, R-CRTCCT4-2, R-CRTCCT4-3: 680K; R_Axial_DIN0516_L15.5mm_D5.0mm_P5.08mm_Vertical
R-CRTCCT4-4: 470K; R_Axial_DIN0516_L15.5mm_D5.0mm_P5.08mm_Vertical
R-CRTCCT4-5: 270K; R_Axial_DIN0516_L15.5mm_D5.0mm_P5.08mm_Vertical
R-CRTCCT4-6: 2M2; R_Axial_DIN0516_L15.5mm_D5.0mm_P5.08mm_Vertical
R-CRTCCT4-7: 22K; R_Axial_DIN0516_L15.5mm_D5.0mm_P5.08mm_Vertical
RV-CRTCCT4-1: 500K; Potentiometer_Bourns_3339P_Vertical_HandSoldering
RV-CRTCCT4-2, RV-CRTCCT4-3: 100K; Potentiometer_Bourns_3339P_Vertical_HandSoldering
V-CRTCCT4-1: VCR97; B12D

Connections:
/CRTCCT4/GND: C-CRTCCT4-1.2, C-CRTCCT4-2.1, C-CRTCCT4-3.1, C-CRTCCT4-6.2, J-CRTCCT4-1.2 (Ext), J-CRTCCT4-6.2 (Ext), J-CRTCCT4-7.2 (Ext), J-CRTCCT4-15.8, R-CRTCCT4-1.2, RV-CRTCCT4-2.1
/CRTCCT4/Heater-6.3V: C-CRTCCT4-4.2, C-CRTCCT4-5.1, D-CRTCCT4-1.1 (J), J-CRTCCT4-15.2, RV-CRTCCT4-3.2, V-CRTCCT4-1.2 (K), V-CRTCCT4-1.3 (h)
/CRTCCT4/Heater-GND: C-CRTCCT4-4.1, D-CRTCCT4-1.3 (J), J-CRTCCT4-15.1, V-CRTCCT4-1.4 (h)
/CRTCCT4/S.EHT(800-1400V): C-CRTCCT4-5.2, C-CRTCCT4-6.1, D-CRTCCT4-1.2 (K), R-CRTCCT4-6.1, R-CRTCCT4-7.1
unnamed: C-CRTCCT4-1.1, R-CRTCCT4-4.1, V-CRTCCT4-1.6 (A2)
unnamed: C-CRTCCT4-2.2, RV-CRTCCT4-2.2, V-CRTCCT4-1.5 (A1), V-CRTCCT4-1.7 (CC), V-CRTCCT4-1.10 (A3)
unnamed: C-CRTCCT4-3.2, J-CRTCCT4-6.1 (In), RV-CRTCCT4-2.3
unnamed: C-CRTCCT4-7.1, J-CRTCCT4-7.1 (In)
unnamed: C-CRTCCT4-7.2, D-CRTCCT4-1.4 (A), R-CRTCCT4-6.2, V-CRTCCT4-1.1 (G1)
unnamed: J-CRTCCT4-2.1, V-CRTCCT4-1.8 (y2)
unnamed: J-CRTCCT4-3.1, V-CRTCCT4-1.12 (y1)
unnamed: J-CRTCCT4-4.1, V-CRTCCT4-1.9 (x2)
unnamed: J-CRTCCT4-5.1, V-CRTCCT4-1.11 (x1)
unnamed: R-CRTCCT4-1.1, R-CRTCCT4-2.2
unnamed: R-CRTCCT4-2.1, R-CRTCCT4-3.2
unnamed: R-CRTCCT4-3.1, RV-CRTCCT4-1.1
unnamed: R-CRTCCT4-4.2, RV-CRTCCT4-1.2
unnamed: R-CRTCCT4-5.1, RV-CRTCCT4-3.1
unnamed: R-CRTCCT4-5.2, RV-CRTCCT4-1.3
unnamed: R-CRTCCT4-7.2, RV-CRTCCT4-3.3

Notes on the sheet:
ASTIG
FOCUS
BRILL

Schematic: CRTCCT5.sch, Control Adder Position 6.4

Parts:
C-CRTCCT5-1: 0.25 4kV; C_Disc_D7.5mm_W5.0mm_P5.00mm
C-CRTCCT5-2, C-CRTCCT5-3, C-CRTCCT5-4: 0.1; C_Disc_D7.5mm_W5.0mm_P5.00mm
C-CRTCCT5-5: 0.5 350V; C_Disc_D7.5mm_W5.0mm_P5.00mm
C-CRTCCT5-6: 0.01 4kV; C_Disc_D7.5mm_W5.0mm_P5.00mm
C-CRTCCT5-7: 0.03 4kv; C_Disc_D7.5mm_W5.0mm_P5.00mm
D-CRTCCT5-1: VR78; Valve_B3G
J-CRTCCT5-1: A.PLATE; 242431
J-CRTCCT5-2: A.Y2; 242431
J-CRTCCT5-3: A.Y1; 242431
J-CRTCCT5-4: A.X2; 242431
J-CRTCCT5-5: A.X1; 242431
J-CRTCCT5-6: +300; 242431
J-CRTCCT5-7: A.GRID; 242431
J-CRTCCT5-16: HIGH Voltage.; TE_MATE-N-LOK_1-770970-x_2x04_P4.14mm_Horizontal
R-CRTCCT5-1, R-CRTCCT5-2, R-CRTCCT5-3: 680K; R_Axial_DIN0516_L15.5mm_D5.0mm_P5.08mm_Vertical
R-CRTCCT5-4: 470K; R_Axial_DIN0516_L15.5mm_D5.0mm_P5.08mm_Vertical
R-CRTCCT5-5: 270K; R_Axial_DIN0516_L15.5mm_D5.0mm_P5.08mm_Vertical
R-CRTCCT5-6: 2M2; R_Axial_DIN0516_L15.5mm_D5.0mm_P5.08mm_Vertical
R-CRTCCT5-7: 22K; R_Axial_DIN0516_L15.5mm_D5.0mm_P5.08mm_Vertical
RV-CRTCCT5-1: 500K; Potentiometer_Bourns_3339P_Vertical_HandSoldering
RV-CRTCCT5-2, RV-CRTCCT5-3: 100K; Potentiometer_Bourns_3339P_Vertical_HandSoldering
V-CRTCCT5-1: VCR97; B12D

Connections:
/CRTCCT5/GND: C-CRTCCT5-1.2, C-CRTCCT5-2.1, C-CRTCCT5-3.1, C-CRTCCT5-6.2, J-CRTCCT5-1.2 (Ext), J-CRTCCT5-6.2 (Ext), J-CRTCCT5-7.2 (Ext), J-CRTCCT5-16.8, R-CRTCCT5-1.2, RV-CRTCCT5-2.1
/CRTCCT5/Heater-6.3V: C-CRTCCT5-4.2, C-CRTCCT5-5.1, D-CRTCCT5-1.1 (J), J-CRTCCT5-16.2, RV-CRTCCT5-3.2, V-CRTCCT5-1.2 (K), V-CRTCCT5-1.3 (h)
/CRTCCT5/Heater-GND: C-CRTCCT5-4.1, D-CRTCCT5-1.3 (J), J-CRTCCT5-16.1, V-CRTCCT5-1.4 (h)
/CRTCCT5/S.EHT(800-1400V): C-CRTCCT5-5.2, C-CRTCCT5-6.1, D-CRTCCT5-1.2 (K), R-CRTCCT5-6.1, R-CRTCCT5-7.1
unnamed: C-CRTCCT5-1.1, R-CRTCCT5-4.1, V-CRTCCT5-1.6 (A2)
unnamed: C-CRTCCT5-2.2, RV-CRTCCT5-2.2, V-CRTCCT5-1.5 (A1), V-CRTCCT5-1.7 (CC), V-CRTCCT5-1.10 (A3)
unnamed: C-CRTCCT5-3.2, J-CRTCCT5-6.1 (In), RV-CRTCCT5-2.3
unnamed: C-CRTCCT5-7.1, J-CRTCCT5-7.1 (In)
unnamed: C-CRTCCT5-7.2, D-CRTCCT5-1.4 (A), R-CRTCCT5-6.2, V-CRTCCT5-1.1 (G1)
unnamed: J-CRTCCT5-2.1, V-CRTCCT5-1.8 (y2)
unnamed: J-CRTCCT5-3.1, V-CRTCCT5-1.12 (y1)
unnamed: J-CRTCCT5-4.1, V-CRTCCT5-1.9 (x2)
unnamed: J-CRTCCT5-5.1, V-CRTCCT5-1.11 (x1)
unnamed: R-CRTCCT5-1.1, R-CRTCCT5-2.2
unnamed: R-CRTCCT5-2.1, R-CRTCCT5-3.2
unnamed: R-CRTCCT5-3.1, RV-CRTCCT5-1.1
unnamed: R-CRTCCT5-4.2, RV-CRTCCT5-1.2
unnamed: R-CRTCCT5-5.1, RV-CRTCCT5-3.1
unnamed: R-CRTCCT5-5.2, RV-CRTCCT5-1.3
unnamed: R-CRTCCT5-7.2, RV-CRTCCT5-3.3

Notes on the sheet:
ASTIG
FOCUS
BRILL

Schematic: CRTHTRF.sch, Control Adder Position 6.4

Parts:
T-CRTHTRF-1: Transformer_1P_3S; JST_EH_B8B-EH-A_1x08_P2.50mm_Vertical

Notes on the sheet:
These windings are at an elevated voltage of -1250v
Mounted at the rear of Rack 5
230v AC

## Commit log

2020-10-08 kvpsu2.pdf
2020-10-08 Add L-STAT.
2020-10-08 System did some house keeping on exit.
2020-10-08 Fix A/B unit switch.
2020-10-09 Add Monicct & MonSW. KiCAD auto changed some of the rest.
2020-10-10 Finish KEYSW2/ Add extra Symbols for switches.
2020-10-11 Expand POWRCTL6b.sch.
    Rearrange Libraries.
2020-10-11 Finish powrctl6b
    Likely wrong bit of it I didn't understand other bits seem wrong inthe orginal.
2020-10-13 Add Prepulse PSEPCTL RMONDRS.
2020-10-13 Add scfollws.sch
2020-10-14 Add sclock correct fault in ACGATE.
2020-10-15 Add SDOT&STB.
2020-10-16 Add sclock, sdot&stb smonxtb
2020-10-17 Add StorGate & some Valve Logic data.
2020-10-18 Add SUBTR1.sch, SXTMBASE.sch TRANSFER.sch.
2020-10-18 Add TYPEWE WRERCCTS YAMP&HVR.
    Which com,pletes the first pass. All the pages are done but I haven't checked them yet and there are bound to be errosr.
2020-10-18 Shrink.
